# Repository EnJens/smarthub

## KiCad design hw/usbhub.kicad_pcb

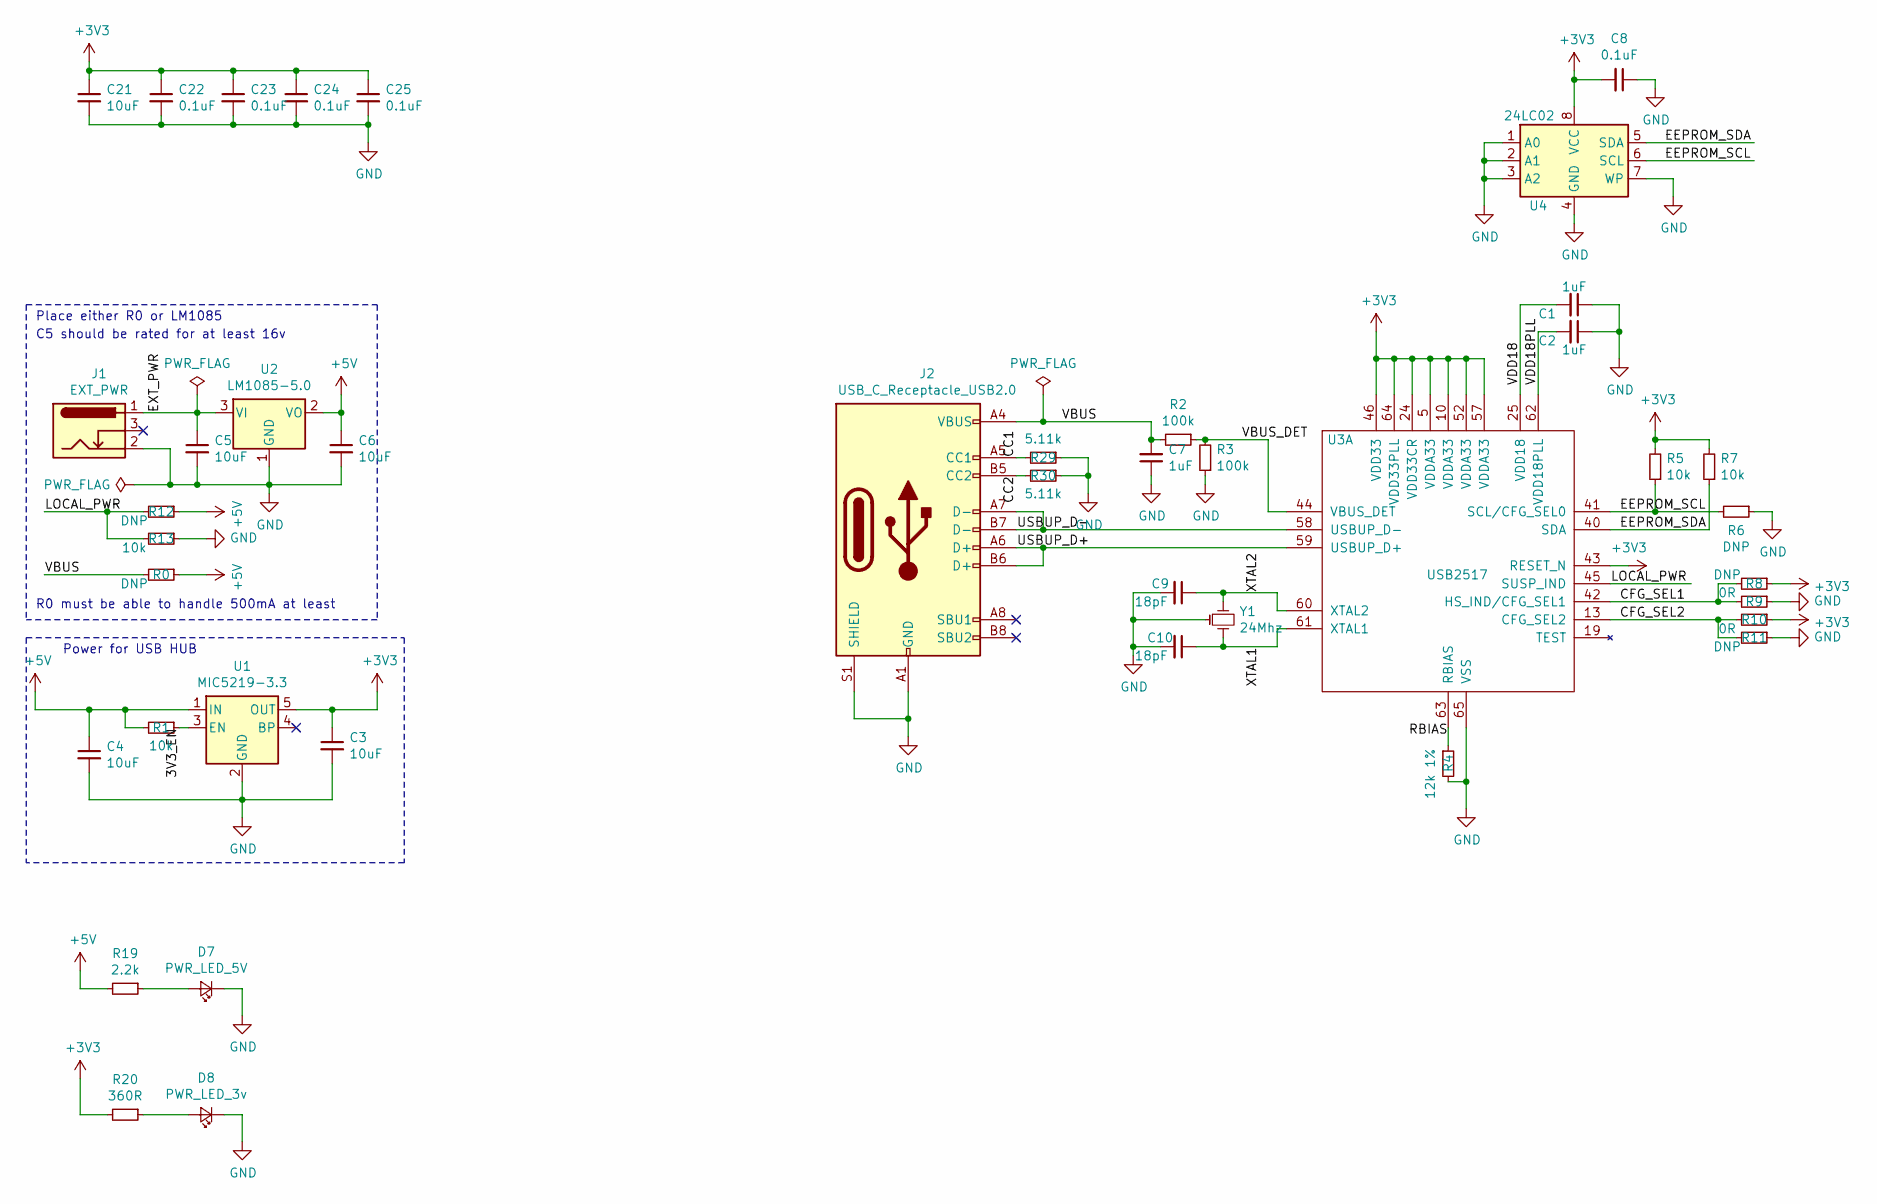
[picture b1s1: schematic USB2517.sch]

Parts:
C1, C2, C7: 1uF; C_0603_1608Metric
C3, C4, C5, C6, C21: 10uF; C_0603_1608Metric
C8, C22, C23, C24, C25: 0.1uF; C_0603_1608Metric
C9, C10: 18pF; C_0603_1608Metric
D7: PWR_LED_5V; LED_0603_1608Metric
D8: PWR_LED_3v; LED_0603_1608Metric
J1: EXT_PWR; Boom_Precision_Elec_DC-005_5.5-2.0MM
J2: USB_C_Receptacle_USB2.0; USB_C_Receptacle_GT-USB-7010
R0: DNP; R_0603_1608Metric
R1, R5, R7: 10k; R_0603_1608Metric
R2, R3: 100k; R_0603_1608Metric
R4: 12k 1%; R_0603_1608Metric
R6, R8, R11, R12: DNP; R_0201_0603Metric
R9, R10: 0R; R_0201_0603Metric
R13: 10k; R_0201_0603Metric
R19: 2.2k; R_0603_1608Metric
R20: 360R; R_0603_1608Metric
R29, R30: 5.11k; R_0603_1608Metric
U1: MIC5219-3.3; SOT-23-5
U2: LM1085-5.0; TO-263-3_TabPin2
U3: USB2517; QFN-64-1EP_9x9mm_P0.5mm_EP4.7x4.7mm_ThermalVias
U4: 24LC02; SOIC-8_3.9x4.9mm_P1.27mm
Y1: 24Mhz; Crystal_SMD_2016-4Pin_2.0x1.6mm

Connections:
+3V3: C3.1, C8.2, C21.1, C22.1, C23.1, C24.1, C25.1, R5.2, R7.2, R8.1, R10.1, R20.2, U1.5 (OUT), U3.5 (VDDA33), U3.10 (VDDA33), U3.24 (VDD33CR), U3.43 (RESET_N), U3.46 (VDD33), U3.52 (VDDA33), U3.57 (VDDA33), U3.64 (VDD33PLL), U4.8 (VCC); also elsewhere on the board
+5V: C4.1, C6.1, R0.1, R1.2, R12.1, R19.2, U1.1 (IN), U2.2 (VO); also elsewhere on the board
/USB2517/3V3_EN: R1.1, U1.3 (EN)
/USB2517/CC1: J2.A5 (CC1), R29.2
/USB2517/CC2: J2.B5 (CC2), R30.2
/USB2517/CFG_SEL1: R8.2, R9.2, U3.42 (HS_IND/CFG_SEL1)
/USB2517/CFG_SEL2: R10.2, R11.2, U3.13 (CFG_SEL2)
/USB2517/EEPROM_SCL: R5.1, R6.2, U3.41 (SCL/CFG_SEL0), U4.6 (SCL)
/USB2517/EEPROM_SDA: R7.1, U3.40 (SDA), U4.5 (SDA)
/USB2517/EXT_PWR: C5.1, J1.1, U2.3 (VI)
/USB2517/LOCAL_PWR: R12.2, R13.2, U3.45 (SUSP_IND)
/USB2517/RBIAS: R4.1, U3.63 (RBIAS)
/USB2517/USBUP_D+: J2.A6 (D+), J2.B6 (D+), U3.59 (USBUP_D+)
/USB2517/USBUP_D-: J2.A7 (D-), J2.B7 (D-), U3.58 (USBUP_D-)
/USB2517/VBUS_DET: R2.1, R3.2, U3.44 (VBUS_DET)
/USB2517/VDD18: C1.2, U3.25 (VDD18)
/USB2517/VDD18PLL: C2.2, U3.62 (VDD18PLL)
/USB2517/XTAL1: C10.1, U3.61 (XTAL1), Y1.2
/USB2517/XTAL2: C9.1, U3.60 (XTAL2), Y1.1
GND: C1.1, C2.1, C3.2, C4.2, C5.2, C6.2, C7.1, C8.1, C9.2, C10.2, C21.2, C22.2, C23.2, C24.2, C25.2, D7.1 (K), D8.1 (K), J1.2, J2.A1 (GND), J2.A12 (GND), J2.B1 (GND), J2.B12 (GND), J2.S1 (SHIELD), R3.1, R4.2, R6.1, R9.1, R11.1, R13.1, R29.1, R30.1, U1.2 (GND), U2.1 (GND), U3.65 (VSS), U4.1 (A0), U4.2 (A1), U4.3 (A2), U4.4 (GND), U4.7 (WP), Y1.3; also elsewhere on the board
unnamed: D7.2 (A), R19.1
unnamed: D8.2 (A), R20.1
VBUS: C7.2, J2.A4 (VBUS), J2.A9 (VBUS), J2.B4 (VBUS), J2.B9 (VBUS), R0.2, R2.2

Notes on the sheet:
Place either R0 or LM1085
R0 must be able to handle 500mA at least
Power for USB HUB
C5 should be rated for at least 16v

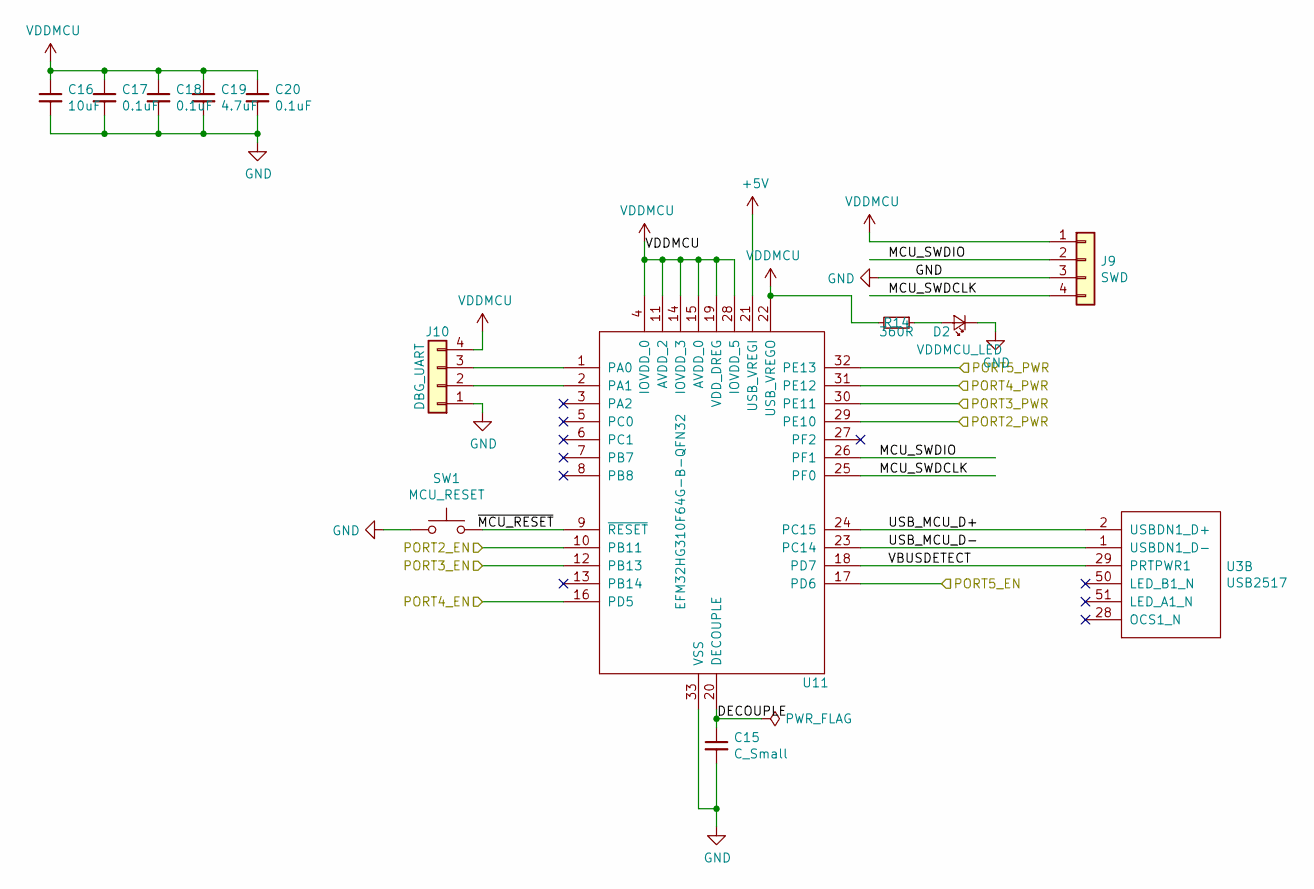
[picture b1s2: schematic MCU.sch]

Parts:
C15: C_Small; C_0603_1608Metric
C16: 10uF; C_0603_1608Metric
C17, C18, C20: 0.1uF; C_0603_1608Metric
C19: 4.7uF; C_0603_1608Metric
D2: VDDMCU_LED; LED_0603_1608Metric
J9: SWD; JST_SH_BM04B-SRSS-TB_1x04-1MP_P1.00mm_Vertical
J10: DBG_UART; JST_SH_BM04B-SRSS-TB_1x04-1MP_P1.00mm_Vertical
R14: 360R; R_0603_1608Metric
SW1: MCU_RESET; SW_SPST_B3U-1000P
U3: USB2517; QFN-64-1EP_9x9mm_P0.5mm_EP4.7x4.7mm_ThermalVias
U11: EFM32HG310F64G-B-QFN32; QFN-32_EP_6x6_Pitch0.65mm

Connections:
+5V: U11.21 (USB_VREGI); also elsewhere on the board
/MCU/DECOUPLE: C15.1, U11.20 (DECOUPLE)
/MCU/MCU_SWDCLK: J9.4, U11.25 (PF0)
/MCU/MCU_SWDIO: J9.2, U11.26 (PF1)
/MCU/PORT2_EN: U11.10 (PB11); also elsewhere on the board
/MCU/PORT2_PWR: U11.29 (PE10); also elsewhere on the board
/MCU/PORT3_EN: U11.12 (PB13); also elsewhere on the board
/MCU/PORT3_PWR: U11.30 (PE11); also elsewhere on the board
/MCU/PORT4_EN: U11.16 (PD5); also elsewhere on the board
/MCU/PORT4_PWR: U11.31 (PE12); also elsewhere on the board
/MCU/PORT5_EN: U11.17 (PD6); also elsewhere on the board
/MCU/PORT5_PWR: U11.32 (PE13); also elsewhere on the board
/MCU/USB_MCU_D+: U3.2 (USBDN1_D+), U11.24 (PC15)
/MCU/USB_MCU_D-: U3.1 (USBDN1_D-), U11.23 (PC14)
/MCU/VBUSDETECT: U3.29 (PRTPWR1), U11.18 (PD7)
/MCU/~MCU_RESET~: SW1.2, U11.9 (~RESET~)
GND: C15.2, C16.2, C17.2, C18.2, C19.2, C20.2, D2.1 (K), J9.3, J10.1, SW1.1, U11.33 (VSS); also elsewhere on the board
unnamed: D2.2 (A), R14.1
unnamed: J10.2, U11.2 (PA1)
unnamed: J10.3, U11.1 (PA0)
VDDMCU: C16.1, C17.1, C18.1, C19.1, C20.1, J9.1, J10.4, R14.2, U11.4 (IOVDD_0), U11.11 (AVDD_2), U11.14 (IOVDD_3), U11.15 (AVDD_0), U11.19 (VDD_DREG), U11.22 (USB_VREGO), U11.28 (IOVDD_5)

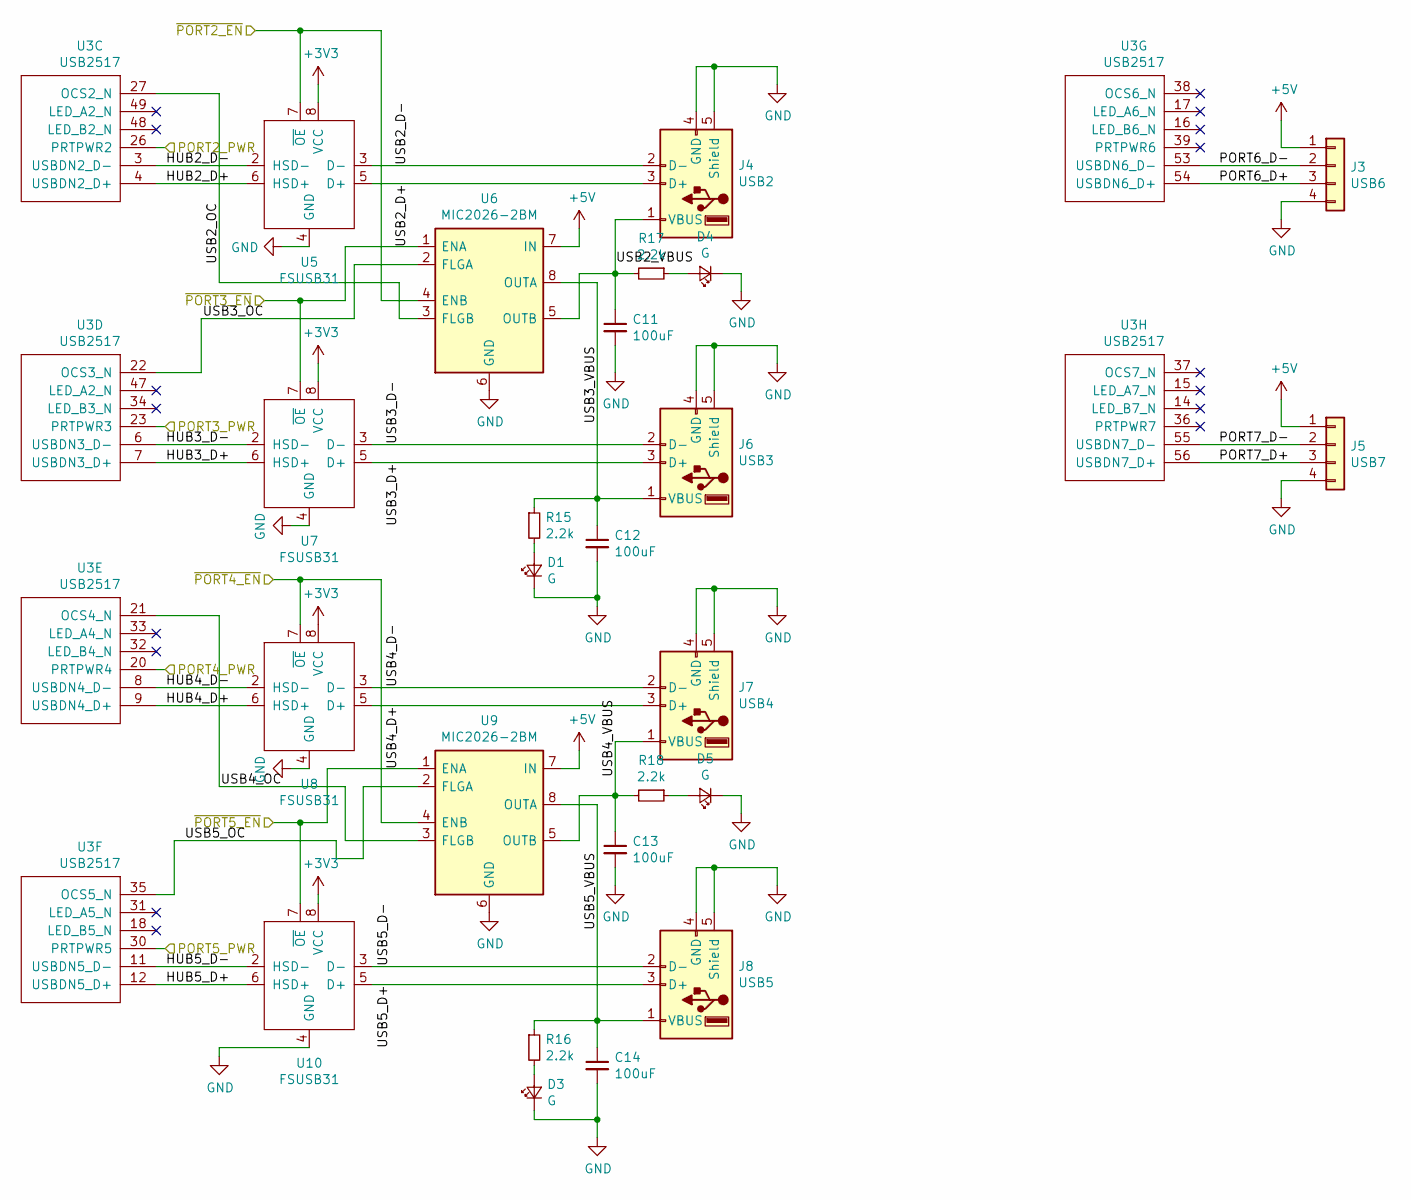
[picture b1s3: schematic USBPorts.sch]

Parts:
C11, C12, C13, C14: 100uF; CP_Elec_5x5.8
D1, D3, D4, D5: G; LED_0603_1608Metric
J3: USB6; PinHeader_1x04_P2.54mm_Vertical
J4: USB2; USB_A_Female_Vertical
J5: USB7; PinHeader_1x04_P2.54mm_Vertical
J6: USB3; USB_A_Female_Vertical
J7: USB4; USB_A_Female_Vertical
J8: USB5; USB_A_Female_Vertical
R15, R16, R17, R18: 2.2k; R_0603_1608Metric
U3: USB2517; QFN-64-1EP_9x9mm_P0.5mm_EP4.7x4.7mm_ThermalVias
U5, U7, U8, U10: FSUSB31; US-8
U6, U9: MIC2026-2BM; SOIC-8_3.9x4.9mm_P1.27mm

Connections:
+3V3: U5.8 (VCC), U7.8 (VCC), U8.8 (VCC), U10.8 (VCC); also elsewhere on the board
+5V: J3.1, J5.1, U6.7 (IN), U9.7 (IN); also elsewhere on the board
/MCU/PORT2_EN: U5.7 (~OE~), U6.4 (ENB); also elsewhere on the board
/MCU/PORT2_PWR: U3.26 (PRTPWR2); also elsewhere on the board
/MCU/PORT3_EN: U6.1 (ENA), U7.7 (~OE~); also elsewhere on the board
/MCU/PORT3_PWR: U3.23 (PRTPWR3); also elsewhere on the board
/MCU/PORT4_EN: U8.7 (~OE~), U9.4 (ENB); also elsewhere on the board
/MCU/PORT4_PWR: U3.20 (PRTPWR4); also elsewhere on the board
/MCU/PORT5_EN: U9.1 (ENA), U10.7 (~OE~); also elsewhere on the board
/MCU/PORT5_PWR: U3.30 (PRTPWR5); also elsewhere on the board
/USBPorts/HUB2_D+: U3.4 (USBDN2_D+), U5.6 (HSD+)
/USBPorts/HUB2_D-: U3.3 (USBDN2_D-), U5.2 (HSD-)
/USBPorts/HUB3_D+: U3.7 (USBDN3_D+), U7.6 (HSD+)
/USBPorts/HUB3_D-: U3.6 (USBDN3_D-), U7.2 (HSD-)
/USBPorts/HUB4_D+: U3.9 (USBDN4_D+), U8.6 (HSD+)
/USBPorts/HUB4_D-: U3.8 (USBDN4_D-), U8.2 (HSD-)
/USBPorts/HUB5_D+: U3.12 (USBDN5_D+), U10.6 (HSD+)
/USBPorts/HUB5_D-: U3.11 (USBDN5_D-), U10.2 (HSD-)
/USBPorts/PORT6_D+: J3.3, U3.54 (USBDN6_D+)
/USBPorts/PORT6_D-: J3.2, U3.53 (USBDN6_D-)
/USBPorts/PORT7_D+: J5.3, U3.56 (USBDN7_D+)
/USBPorts/PORT7_D-: J5.2, U3.55 (USBDN7_D-)
/USBPorts/USB2_D+: J4.3 (D+), U5.5 (D+)
/USBPorts/USB2_D-: J4.2 (D-), U5.3 (D-)
/USBPorts/USB2_OC: U3.27 (OCS2_N), U6.3 (FLGB)
/USBPorts/USB2_VBUS: C11.1, J4.1 (VBUS), R17.2, U6.5 (OUTB)
/USBPorts/USB3_D+: J6.3 (D+), U7.5 (D+)
/USBPorts/USB3_D-: J6.2 (D-), U7.3 (D-)
/USBPorts/USB3_OC: U3.22 (OCS3_N), U6.2 (FLGA)
/USBPorts/USB3_VBUS: C12.1, J6.1 (VBUS), R15.1, U6.8 (OUTA)
/USBPorts/USB4_D+: J7.3 (D+), U8.5 (D+)
/USBPorts/USB4_D-: J7.2 (D-), U8.3 (D-)
/USBPorts/USB4_OC: U3.21 (OCS4_N), U9.3 (FLGB)
/USBPorts/USB4_VBUS: C13.1, J7.1 (VBUS), R18.2, U9.5 (OUTB)
/USBPorts/USB5_D+: J8.3 (D+), U10.5 (D+)
/USBPorts/USB5_D-: J8.2 (D-), U10.3 (D-)
/USBPorts/USB5_OC: U3.35 (OCS5_N), U9.2 (FLGA)
/USBPorts/USB5_VBUS: C14.1, J8.1 (VBUS), R16.1, U9.8 (OUTA)
GND: C11.2, C12.2, C13.2, C14.2, D1.1 (K), D3.1 (K), D4.1 (K), D5.1 (K), J3.4, J4.4 (GND), J4.5 (Shield), J5.4, J6.4 (GND), J6.5 (Shield), J7.4 (GND), J7.5 (Shield), J8.4 (GND), J8.5 (Shield), U5.4 (GND), U6.6 (GND), U7.4 (GND), U8.4 (GND), U9.6 (GND), U10.4 (GND); also elsewhere on the board
unnamed: D1.2 (A), R15.2
unnamed: D3.2 (A), R16.2
unnamed: D4.2 (A), R17.1
unnamed: D5.2 (A), R18.1

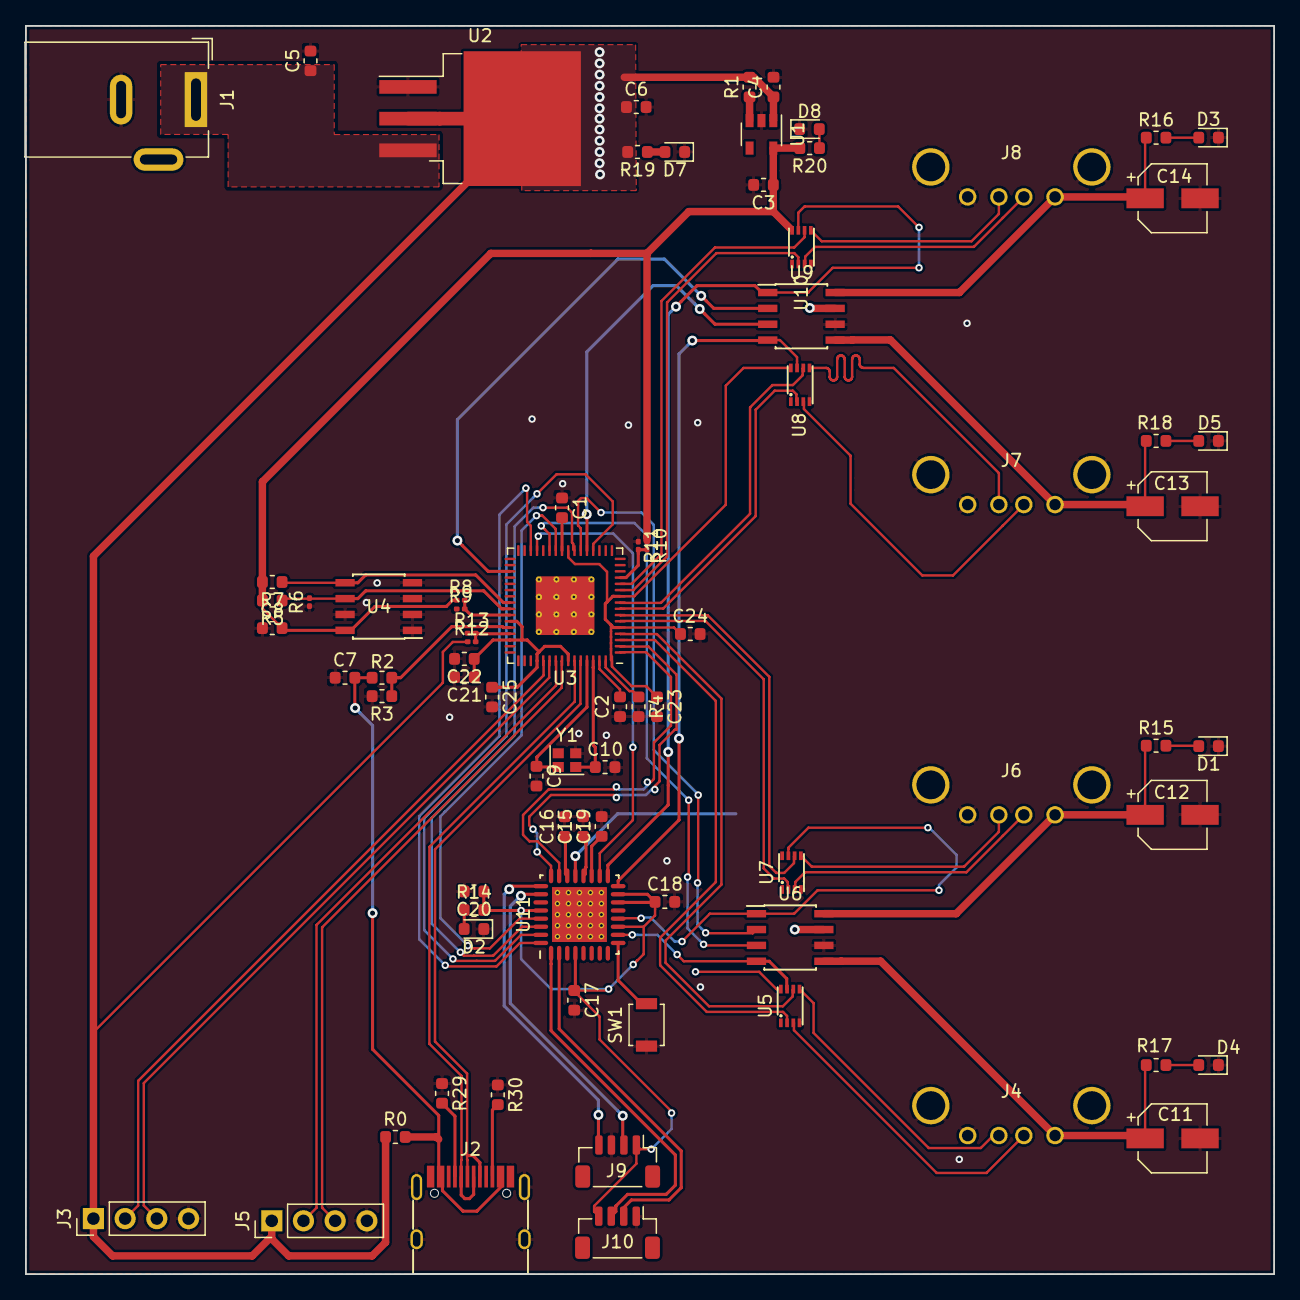
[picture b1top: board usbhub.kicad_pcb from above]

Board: 2 copper layers, 100.0 x 100.0 mm, 78 parts (0 on the bottom side), 74 nets.

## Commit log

2018-02-05 Initial version with USB2517 symbol
2018-02-05 Add Microchip USB2517 datasheet
2018-02-08 Add more datasheets
2018-02-08 Remove useless file
2018-09-09 Improve usb2517 footprint
2018-09-09 Add more
2018-09-20 Finish up usb port hookup
2018-10-13 minor fixes
2018-10-28 Finalize schematics
2018-10-28 Add most footprints, switch to usb c
2018-10-30 Add footprints to everything else, except barrel jack
2018-10-30 Add 3d models
2018-10-30 Add the remaining 3d models
2018-11-12 Begin routing
2018-11-18 More parts placement
2018-11-28 More placement, more issues
2018-12-03 More routing, simplification
2018-12-05 Final
2018-12-05 Rename project
2018-12-05 Add Revision A gerbers
2018-12-13 Add InteractiveHTMLBom
